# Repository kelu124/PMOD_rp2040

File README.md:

# Modules for signal acquisition and transmission - using the PMOD standard  

PMODs for my rp2040-based boards

# List of PMODs

## HVPulser + HV Source

## PSRAM

## R2R DAC

## FT4222 - _Untested yet_

## 6-bit VGA

# License

This work is based on previous TAPR projects, [the echOmods project](https://github.com/kelu124/echomods/), the [un0rick project](https://doi.org/10.5281/zenodo.377054), and the [lit3rick project](https://doi.org/10.5281/zenodo.5792245) - their boards are open hardware and software, developped with open-source elements as much as possible.

Copyright Luc Jonveaux (<kelu124@gmail.com>) 2024

* The hardware is licensed under TAPR Open Hardware License (<www.tapr.org/OHL>)
* The software components are free software: you can redistribute it and/or modify it under the terms of the GNU General Public License as published by the Free Software Foundation, either version 3 of the License, or (at your option) any later version.
* The documentation is licensed under a [Creative Commons Attribution-ShareAlike 3.0 Unported License](http://creativecommons.org/licenses/by-sa/3.0/).

## Disclaimer

This project is distributed WITHOUT ANY EXPRESS OR IMPLIED WARRANTY, INCLUDING OF MERCHANTABILITY, SATISFACTORY QUALITY AND FITNESS FOR A PARTICULAR PURPOSE.

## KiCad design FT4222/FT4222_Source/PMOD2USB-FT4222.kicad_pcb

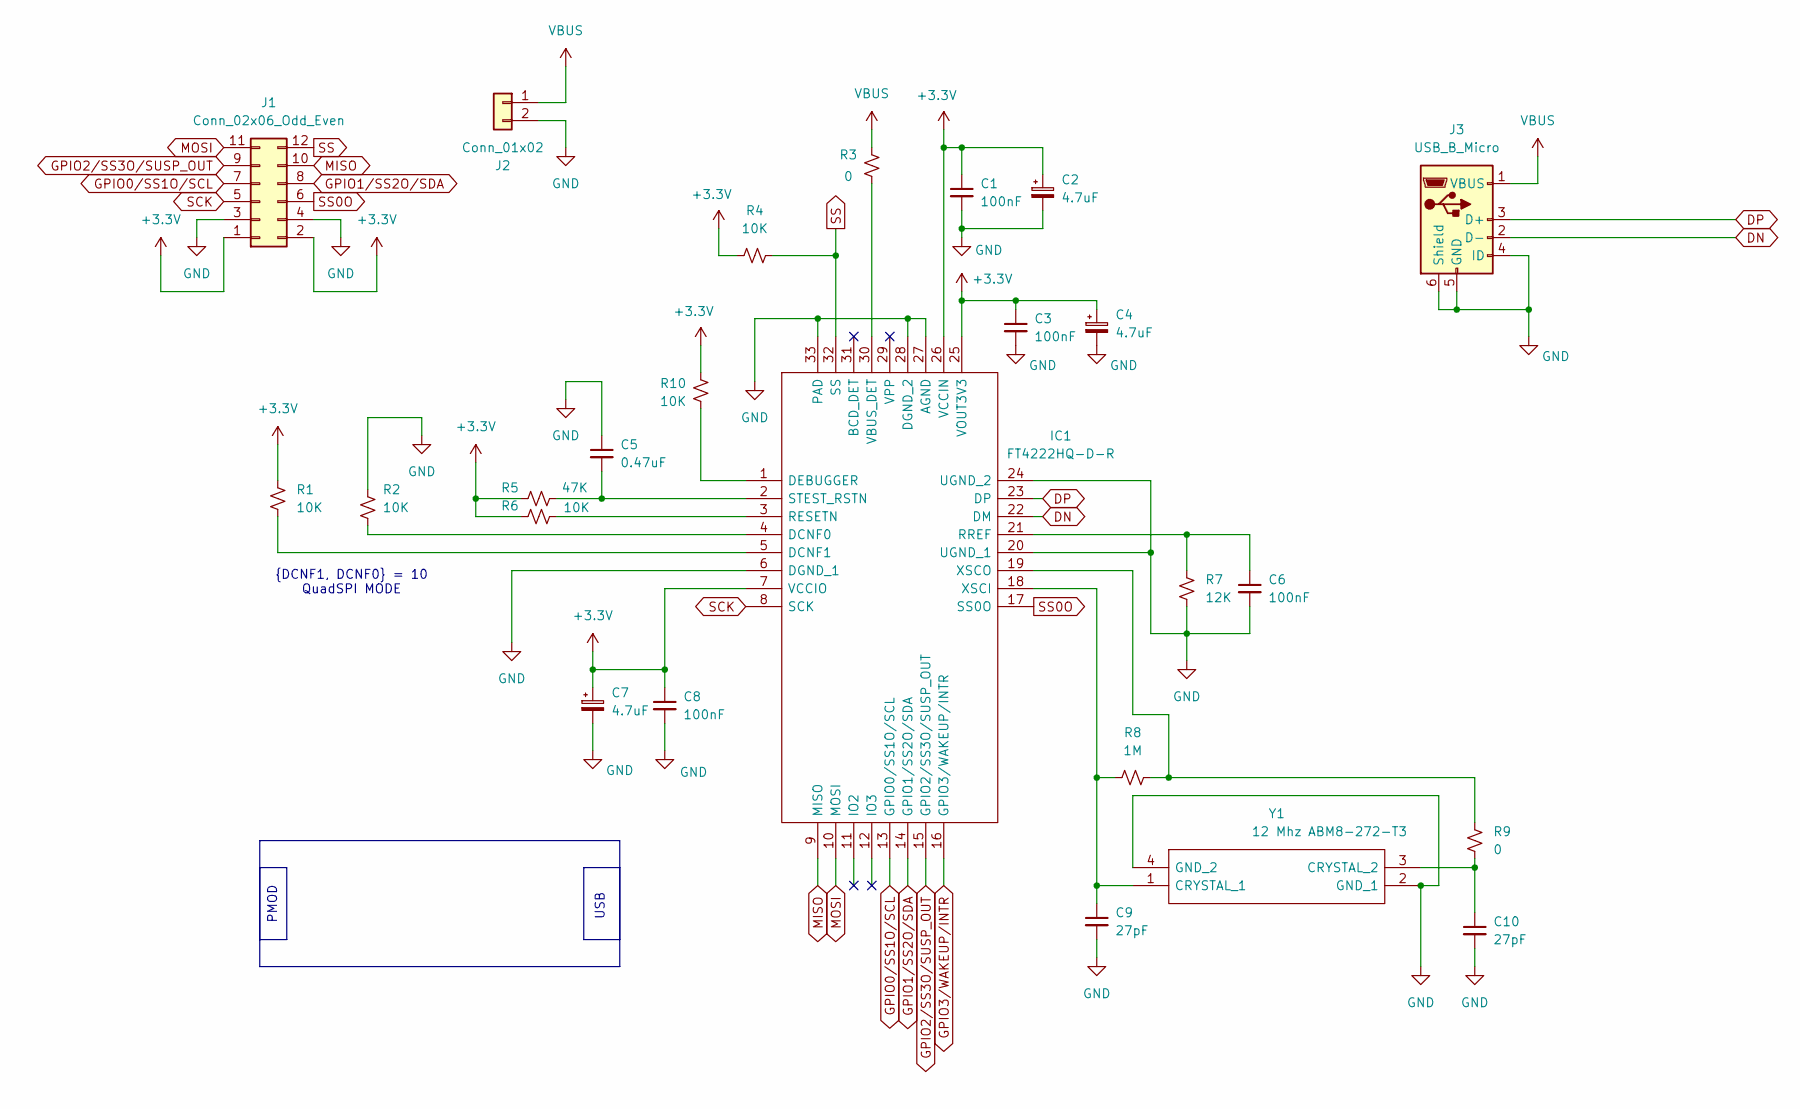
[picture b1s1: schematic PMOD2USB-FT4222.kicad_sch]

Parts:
C1, C3, C6, C8: 100nF; C_1206_3216Metric
C2, C4, C7: 4.7uF; C_1206_3216Metric
C5: 0.47uF; C_1206_3216Metric
C9, C10: 27pF; C_1206_3216Metric
IC1: FT4222HQ-D-R; QFN50P500X500X90-33N; Mouser Part Number 895-FT4222HQ-D-R
J1: Conn_02x06_Odd_Even; PinHeader_2x06_P2.54mm_Horizontal
J2: Conn_01x02; PinHeader_2x01_P2.54mm_Horizontal
J3: USB_B_Micro; USB_Micro-B_Amphenol_10118193-0001LF_Horizontal
R1, R2, R4, R6, R10: 10K; R_1206_3216Metric
R3, R9: 0; R_1206_3216Metric
R5: 47K; R_1206_3216Metric
R7: 12K; R_1206_3216Metric
R8: 1M; R_1206_3216Metric
Y1: 12 Mhz; ABM8272T3; Mouser Part Number 815-ABM8-272-T3

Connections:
+3.3V: C1.1, C2.1, C3.1, C4.1, C7.1, C8.1, IC1.7 (VCCIO), IC1.25 (VOUT3V3), IC1.26 (VCCIN), J1.1, J1.2, R1.1, R4.1, R5.1, R6.1, R10.2
DN: IC1.22 (DM), J3.2 (D-)
DP: IC1.23 (DP), J3.3 (D+)
GND: C1.2, C2.2, C3.2, C4.2, C5.1, C6.2, C7.2, C8.2, C9.2, C10.2, IC1.6 (DGND_1), IC1.20 (UGND_1), IC1.24 (UGND_2), IC1.27 (AGND), IC1.28 (DGND_2), IC1.33 (PAD), J1.3, J1.4, J2.2, J3.4 (ID), J3.5 (GND), J3.6 (Shield), R2.1, R7.2, Y1.2 (GND_1), Y1.4 (GND_2)
GPIO0/SS1O/SCL: IC1.13 (GPIO0/SS1O/SCL), J1.7
GPIO1/SS2O/SDA: IC1.14 (GPIO1/SS2O/SDA), J1.8
GPIO2/SS3O/SUSP_OUT: IC1.15 (GPIO2/SS3O/SUSP_OUT), J1.9
GPIO3/WAKEUP/INTR: IC1.16 (GPIO3/WAKEUP/INTR)
MISO: IC1.9 (MISO), J1.10
MOSI: IC1.10 (MOSI), J1.11
unnamed: IC1.4 (DCNF0), R2.2
unnamed: IC1.5 (DCNF1), R1.2
unnamed: IC1.1 (DEBUGGER), R10.1
unnamed: IC1.3 (RESETN), R6.2
unnamed: C6.1, IC1.21 (RREF), R7.1
unnamed: C5.2, IC1.2 (STEST_RSTN), R5.2
unnamed: IC1.30 (VBUS_DET), R3.1
unnamed: C9.1, IC1.18 (XSCI), R8.1, Y1.1 (CRYSTAL_1)
unnamed: IC1.19 (XSCO), R8.2, R9.2
unnamed: C10.1, R9.1, Y1.3 (CRYSTAL_2)
SCK: IC1.8 (SCK), J1.5
SS: IC1.32 (SS), J1.12, R4.2
SS0O: IC1.17 (SS0O), J1.6
VBUS: J2.1, J3.1 (VBUS), R3.2

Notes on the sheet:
USB
PMOD
{DCNF1, DCNF0} = 10 QuadSPI MODE

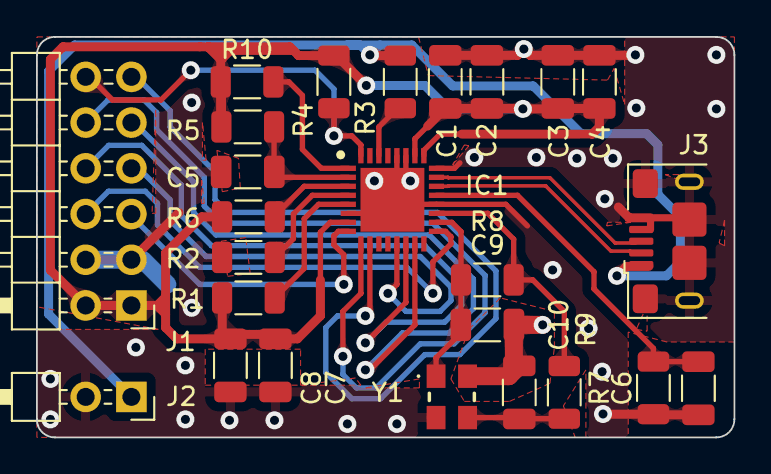
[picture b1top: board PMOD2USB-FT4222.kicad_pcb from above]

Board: 2 copper layers, 38.8 x 22.2 mm, 25 parts (0 on the bottom side), 23 nets.

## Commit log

2024-04-20 New PMODs
2024-04-20 Adding pics
2024-04-20 Working R2R, albeil slown 2.5Msps
2024-04-22 New pulse sequence
2024-04-22 R2R confirmed 16msps
2024-05-08 autoupdate
